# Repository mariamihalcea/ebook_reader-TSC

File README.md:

# OpenBook E-Reader 

## 1. Diagrama bloc

**Descriere:**

- Microcontrollerul **ESP32-C6** este unitatea centrala care gestioneaza comunicarea cu toate modulele periferice.
- Display-ul e-paper este controlat de un circuit dedicat de comanda.
- Senzorul ambiental **BME688** masoara calitatea aerului si temperatura.
- Memoria externa NOR Flash (64MB) si cardul SD permit stocarea fisierelor (eBook-uri, configurari etc).
- RTC-ul **DS3231SN** asigura ora exacta in mod autonom, chiar si in lipsa alimentarii.
- Incarcarea bateriei Li-Po se face prin USB-C, cu protectie ESD si monitorizare a nivelului de incarcare (MAX17048).
- Butoanele fizice permit resetul sistemului si selectii de tip boot.

---

## 2. Bill Of Materials (BOM)
| Componenta | Link | Datasheet |
|-----------|--------------|-----------|
| BUTTON | [Model](https://industry.panasonic.com/global/en/products/control/switch/light-touch/number/evqpuj02k) | [Datasheet](https://www.lcsc.com/datasheet/lcsc_datasheet_2201121800_PANASONIC-EVQPUJ02K_C2936858.pdf) |
| CAPACITOR | [Model](https://componentsearchengine.com/part-view/R0402%201%25%20100%20K%20(RC0402FR-07100KL)/YAGEO) | [Datasheet](//efaidnbmnnnibpcajpcglclefindmkaj/https://www.resistor.com/assets/pdf/0402tstd.pdf) |
| CPH3225A | [Model](https://www.snapeda.com/parts/CPH3225A/Seiko+Instruments/view-part/?ref=eda) | [Datasheet](https://octopart.com/datasheet/cph3225a-seiko-25340571) |
| EVQPUJ02K | [Model](https://industry.panasonic.com/global/en/products/control/switch/light-touch/number/evqpuj02k) | [Datasheet](https://www.lcsc.com/datasheet/lcsc_datasheet_2201121800_PANASONIC-EVQPUJ02K_C2936858.pdf) |
| KP-1608SURCK | [Model](https://www.snapeda.com/parts/KP-1608SURCK/Kingbright/view-part/?ref=search&t=LED%200603) | [Datasheet](//efaidnbmnnnibpcajpcglclefindmkaj/https://media.elv.com/file/107153_led_surck1608_data.pdf) |
| USBLC6-2SC6Y | [Model](https://www.snapeda.com/parts/USBLC6-2SC6Y/STMicroelectronics/view-part/?ref=eda) | [Datasheet](https://www.digikey.com/en/htmldatasheets/production/1375342/0/0/1/usblc6-2sc6y) |
| SD0805S020S1R0 | [Model](https://ro.mouser.com/ProductDetail/KYOCERA-AVX/SD0805S020S1R0?qs=jCA%252BPfw4LHbpkAoSnwrdjw%3D%3D) | [Datasheet](https://www.alldatasheet.com/view.jsp?Searchword=SD0805S&sField=2) |
| PGB1010603MR | [Model](https://www.snapeda.com/parts/PGB1010603MR/Littelfuse/view-part/?ref=eda) | [Datasheet](https://www.alldatasheet.com/view.jsp?Searchword=Pgb1010603mr&gad_source=1&gbraid=0AAAAADcdDU8aYfZtfJfdZ9I5j6RwZ_cbA&gclid=Cj0KCQjwqcO_BhDaARIsACz62vOPBOBe0eOh5gDUFkkKl4JBcbmoFZYtJ8BOnbaWqr_BuUCcVWvbutAaAmGkEALw_wcB) |
| BD5229G-TR  | [Model](https://componentsearchengine.com/part-view/BD5229G-TR/ROHM%20Semiconductor) | [Datasheet](https://www.lcsc.com/datasheet/lcsc_datasheet_2201131330_ROHM-Semicon-BD5229G-TR_C962636.pdf) |
| XC6220A331MR-G | [Model](https://componentsearchengine.com/part-view/XC6220A331MR-G/Torex) | [Datasheet](https://www.alldatasheet.com/view.jsp?Searchword=Xc6220&gad_source=1&gbraid=0AAAAADcdDU8aYfZtfJfdZ9I5j6RwZ_cbA&gclid=Cj0KCQjwqcO_BhDaARIsACz62vPS06NB6tLgniZzfaVpKNu1m811BNk6AEPfg4DbP6f5S8QWA_pW_UQaAv-0EALw_wcB) |
| XC6220A331MR-G | [Model](https://componentsearchengine.com/part-view/XC6220A331MR-G/Torex) | [Datasheet](https://www.alldatasheet.com/view.jsp?Searchword=Xc6220&gad_source=1&gbraid=0AAAAADcdDU8aYfZtfJfdZ9I5j6RwZ_cbA&gclid=Cj0KCQjwqcO_BhDaARIsACz62vMO5_aHsn35cIZBK6oCFuB_WOxz_zKu4yOHJ69-EnaUd5Jfas_Avm8aAuk5EALw_wcB) |
| USB4110-GF-A  | [Model](https://componentsearchengine.com/part-view/USB4110-GF-A/GCT%20(GLOBAL%20CONNECTOR%20TECHNOLOGY)) | [Datasheet](//efaidnbmnnnibpcajpcglclefindmkaj/https://gct.co/files/drawings/usb4110.pdf) |
| Adafruit | [Model](https://eu.mouser.com/ProductDetail/Adafruit/4208?qs=PzGy0jfpSMtbScLbr0L5dw%3D%3D) | [Datasheet](https://www.arrow.com/en/manufacturers/adafruit-industries/datasheets) |
| Bobina | [Model](https://store.comet.srl.ro/Catalogue/Product/43497/) | [Datasheet](https://www.scribd.com/document/814581278/Datasheet-Bobina) |
| PFMF | [Model](https://www.mouser.co.uk/ProductDetail/EPCOS-TDK/B72520T0350K062?qs=dEfas%2FXlABIszF52uu7vrg%3D%3D) | [Datasheet](https://ro.mouser.com/c/ds/circuit-protection/thermistors/resettable-fuses-pptc/?m=Schurter&series=PFMF) |
| DMG2305UX-7 | [Model](https://componentsearchengine.com/part-view/DMG2305UX-7/Diodes%20Incorporated) | [Datasheet](//efaidnbmnnnibpcajpcglclefindmkaj/https://www.mouser.com/datasheet/2/115/DMG2305UX-266242.pdf?srsltid=AfmBOop22k34YTJJra1xubiU6LPiN4M4JlcWbRoSNdxSGFak8uWgXPpK) |
| Si1308EDL-T1-GE3 | [Model](https://componentsearchengine.com/part-view/SI1308EDL-T1-GE3/Vishay) | [Datasheet](https://www.alldatasheet.com/view.jsp?Searchword=Si1308edl&gad_source=1&gbraid=0AAAAADcdDU-px713ONYSnQ2O-gcwqYcFq&gclid=Cj0KCQjwqcO_BhDaARIsACz62vN_Nz3MJOc6J_03gnVBm7aSqC8v9wyP0VD-iRKP-gFrYgdhLi99I14aAlVJEALw_wcB) |
| R0402 | [Model](https://componentsearchengine.com/part-view/R0402%201%25%20100%20K%20(RC0402FR-07100KL)/YAGEO) | [Datasheet](//efaidnbmnnnibpcajpcglclefindmkaj/https://www.resistor.com/assets/pdf/0402tstd.pdf) |
| BME680 | [Model](https://www.snapeda.com/parts/BME680/Bosch/view-part/?welcome=home) | [Datasheet](//efaidnbmnnnibpcajpcglclefindmkaj/https://www.bosch-sensortec.com/media/boschsensortec/downloads/datasheets/bst-bme680-ds001.pdf) |
| SMD Solder | [Model](https://grabcad.com/library/solder-jumpers-1) | [Datasheet]() |
| W25Q512JVEIQ | [Model](https://www.snapeda.com/parts/ESP32-C6-WROOM-1-N8/Espressif+Systems/view-part/?ref=eda) | [Datasheet](//efaidnbmnnnibpcajpcglclefindmkaj/https://www.mouser.com/datasheet/2/949/W25Q512JV_SPI_RevB_06252019_KMS-2487502.pdf?srsltid=AfmBOoquExqDVgxEELF9CzuOGxHos0CD1nQDROHD6Eebdm2foNzqozqU) |
| ESP32-C6-WROOM-1-N8 | [Model](https://www.snapeda.com/parts/ESP32-C6-WROOM-1-N8/Espressif+Systems/view-part/?ref=eda) | [Datasheet](//efaidnbmnnnibpcajpcglclefindmkaj/https://www.mouser.com/catalog/specsheets/Espressif_ESP32_C6_WROOM_1%20_Datasheet_V0.1_PRELIMINARY_en.pdf?srsltid=AfmBOooHQKNitqODRaaPjoZInfWKTacDER1t5uRK6sKqT13TrzvVo_B7) |
| DS3231SN# | [Model](https://www.snapeda.com/parts/DS3231SN%23/Analog+Devices/view-part/?ref=eda) | [Datasheet](https://www.alldatasheet.com/view.jsp?Searchword=Ds3231sn%20datasheet&gad_source=1&gbraid=0AAAAADcdDU-Gy9URfMxGmqiPg7ci5L3wR&gclid=Cj0KCQjwqcO_BhDaARIsACz62vMkK3ETSnW2w7mo0Fa-wgWJGn89AxWCyIND6k5X8MmoPl6hv6VWwT8aAiS-EALw_wcB) |
| MAX17048G+T10 | [Model](https://www.snapeda.com/parts/MAX17048G+T10/Analog+Devices/view-part/?ref=eda) | [Datasheet](https://www.alldatasheet.com/view.jsp?Searchword=Max17048&gad_source=1&gbraid=0AAAAADcdDU8aYfZtfJfdZ9I5j6RwZ_cbA&gclid=Cj0KCQjwqcO_BhDaARIsACz62vNa9xrVfzjCjADRwXD0RBbo4Nret3ywwteDGLJKZui8ZL8KdVlTE7caAvQxEALw_wcB) |
| MCP73831T-5ACI/OT | [Model](https://www.mouser.co.uk/ProductDetail/Microchip-Technology/MCP73831T-5ACI-OT?qs=hH%252BOa0VZEiAcgAcEkuamXg%3D%3D) | [Datasheet](//efaidnbmnnnibpcajpcglclefindmkaj/https://ww1.microchip.com/downloads/en/DeviceDoc/MCP73831-Family-Data-Sheet-DS20001984H.pdf) |

## 3. Descriere hardware detaliata

###  Microcontroller – ESP32-C6
- Controleaza toate componentele externe prin GPIO, I2C, SPI.

### E-paper Display + Driver
- Controlat prin SPI, cu tensiune separata de alimentare si control.

###  RTC – DS3231SN
- Ceas in timp real cu precizie mare si backup pe baterie.
- Comunicatie I2C cu ESP32-C6.
- Folosit pentru afisarea orei si sincronizare evenimente programate.

### Card SD
- Legat la ESP32 prin SPI.
- Utilizat pentru incarcare/citire fisiere eBook, configurari etc.

###  Senzor mediu – BME688
- Comunica prin I2C.
- Masoara temperatura, presiune, umiditate si compusi volatili.

###  Conector USB-C
- Folosit pentru incarcare si posibila conectare seriala cu PC pentru debug.

##  4. Conexiuni ESP32-C6

| Componenta            | Pin ESP32-C6      | Interfata | Motiv utilizare                      |
|----------------------|-------------------|-----------|--------------------------------------|
| E-paper Display       | IO06, IO07, IO08  | SPI       | Transfer rapid de date catre display |
| Flash NOR             | IO10, IO11, IO12  | SPI       | Stocare externa rapida               |
| Senzor BME688         | IO18 (SDA), IO19 (SCL) | I2C   | Comunicare cu senzori               |
| RTC DS3231SN          | IO18, IO19        | I2C       | Reutilizeaza magistrala I2C         |
| MAX17048 (Baterie)    | IO18, IO19        | I2C       | Monitor baterie, I2C comun           |
| SD Card               | IO01, IO02, IO03  | SPI       | Citire fisiere eBook                 |
| Buton reset/boot      | IO00, EN          | GPIO      | Control boot si reset manual        |

---

## 5. Pasi de implementare

### 1. Analiza documentatiei initiale
Am analizat schematicul si layout-ul placii furnizate de profesor. Pe baza acestora, am recreat designul electronic in Fusion Electronics, atat schema electrica, cat si placa PCB.

### 2. Plasarea componentelor pe PCB
Am asezat componentele pe placa, urmarind o pozitionare si orientare optime, pentru a permite o rutare eficienta si functionala.

### 3. Rutarea traseelor
Traseele de alimentare au fost rutate manual pentru a asigura robustete si dimensiuni corecte. Conexiunile ramase au fost rutate automat, folosind functia de autorouting pe ambele straturi (top si bottom). Am adaugat polygon pour pentru a crea plane de masa pe ambele straturi.

### 4. Optimizarea layout-ului
Am folosit vias pentru a conecta planele de masa intre straturi si pentru a completa zonele neconectate. Am aplicat via stitching pentru a imbunatati integritatea electrica a designului.

### 5. Generarea modelului 3D al placii
Pe baza designului 2D, am generat modelul 3D al placii. Am cautat si importat manual fiecare componenta 3D, pozitionandu-le conform plasamentului din PCB-ul 2D. Pentru componenta *test pad*, neavand un model disponibil online, am creat manual unul pentru a reprezenta corect placa in ansamblu.

### 6. Integrarea in ansamblul final – OpenBook Enclosure
Am importat modelul 3D al placii in fisierul principal al carcasei (OpenBook Enclosure). Acolo am plasat toate componentele in carcasa finala pentru a asigura o potrivire corecta si functionala. Display-ul si bateria au fost desenate manual pentru a fi integrate in ansamblu si pentru a oferi o reprezentare cat mai realista a produsului final.
##  6. Alte detalii relevante

La realizarea PCB-ului am intampinat si doua erori de Copper Width, desi aveam  dimensiunile corespunzatoare, asa ca le-am aprobat.

<br>
si doua erori din cauza dimensiunii gaurilor din mufa USB, pe care de asemenea le am aprobat

---

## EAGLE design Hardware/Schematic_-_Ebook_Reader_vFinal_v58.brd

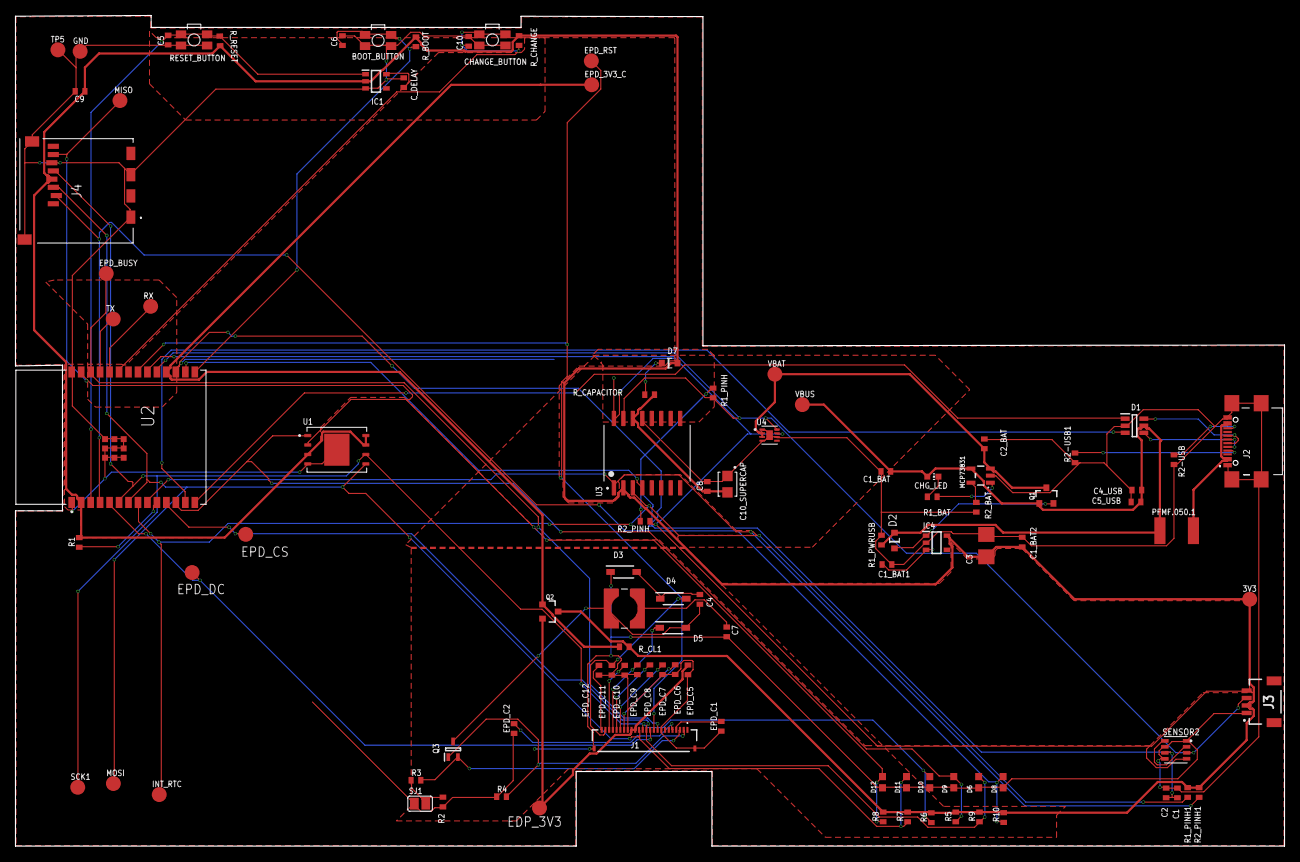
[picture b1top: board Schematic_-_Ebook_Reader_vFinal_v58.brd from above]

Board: 2 copper layers, 170.2 x 111.4 mm, 103 parts (0 on the bottom side), 57 nets.

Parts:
3V3: TPTP20R; TP20R
BOOT_BUTTON: BUTTON_CUSYOMV1; MYBUTTON
C1, C2, C4_USB, C6, C8, C9, C10: 100nF; EAGLE-LTSPICE_C0402
C1_BAT, C1_BAT1, C1_BAT2, C2_BAT, C5_USB: 4.7uF; EAGLE-LTSPICE_C0402
C3: 100uF TANT; RCL_CT3528
C4: 4.7uF/25V; EAGLE-LTSPICE_C0402
C5: 1uF; EAGLE-LTSPICE_C0402
C7: 10uF; EAGLE-LTSPICE_C0402
C10_SUPERCAP: CPH3225A; CAPCP3225X100N
CHANGE_BUTTON: BUTTON_CUSYOMV1; MYBUTTON
CHG_LED: ADAFRUIT_CHIP-LED0603
C_DELAY: 100nF; EAGLE-LTSPICE_C0402
D1: USBLC6-2SC6Y; SOT95P280X145-6N
D2, D7: ESP32_WROVER_AVX---SD0805S020S1R0_AVX_SD0805S020S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; ESP32_WROVER_AVX---SD0805S020S1R0_AVX_SD0805S020S1R0_0
D3, D4, D5: MBR0530; SOD3716X135N
D6, D8, D9, D10, D11, D12: PGB1010603MR; DIOC1608X36N
EDP_3V3: TPTP20R; TP20R
EPD_3V3_C: TPTP20R; TP20R
EPD_BUSY: TPTP20R; TP20R
EPD_C1, EPD_C2, EPD_C6, EPD_C7, EPD_C8, EPD_C9, EPD_C10, EPD_C11: 1uF_50V; EAGLE-LTSPICE_C0402
EPD_C5: 0.1uF_50V; EAGLE-LTSPICE_C0402
EPD_C12: 1uF/50v; EAGLE-LTSPICE_C0402
EPD_CS: TPTP20R; TP20R
EPD_DC: TPTP20R; TP20R
EPD_RST: TPTP20R; TP20R
GND: TPTP20R; TP20R
IC1: BD5229G-TR; SOT95P280X125-5N
IC4: XC6220A331MR-G; SOT95P280X120-5N
INT_RTC: TPTP20R; TP20R
J1: FH34SRJ-24S-0.5SH_99_; FH34SRJ24S05SH99
J2: SAMACSYS_PARTS_USB4110-GF-A; SAMACSYS_PARTS_USB4110GFA
J3: QWIIC_RIGHT_ANGLE; JST04_1MM_RA
J4: 112A-TAAR-R03_ATTEND; 112ATAARR03ATTEND
L1: 68uH; IND_4828-WE-TPC_WRE
MCP73831: ESP32_WROVER_SPARKFUN-IC-POWER_MCP73831; ESP32_WROVER_SPARKFUN-IC-POWER_SOT23-5
MISO: TPTP20R; TP20R
MOSI: TPTP20R; TP20R
PFMF.050.1: ESP32C6_VARISTORCN1812; ESP32C6_VARISTOR_CT/CN1812
Q1, Q2: 20V/4.2A/52mΩ/1.4W; ESP32_WROVER_SPARKFUN-DISCRETESEMI_SOT23-3
Q3: SI1308EDL-T1-GE3; SOT65P210X110-3N
R1, R1_PINH, R1_PINH1, R4, R5, R6, R7, R8, R9, R10: 10K; ESP32_WROVER_EAGLE-LTSPICE_R0402
R1_BAT: 200; ESP32_WROVER_EAGLE-LTSPICE_R0402
R1_PWRUSB: 100K; ESP32_WROVER_EAGLE-LTSPICE_R0402
R2: 2.2; ESP32_WROVER_EAGLE-LTSPICE_R0402
R2-USB, R2-USB1: 5k1; ESP32_WROVER_EAGLE-LTSPICE_R0402
R2_BAT: 2K; ESP32_WROVER_EAGLE-LTSPICE_R0402
R2_PINH, R2_PINH1: 10k; ESP32_WROVER_EAGLE-LTSPICE_R0402
R3: 0.47; ESP32_WROVER_EAGLE-LTSPICE_R0402
RESET_BUTTON: BUTTON_CUSYOMV1; MYBUTTON
RX: TPTP20R; TP20R
R_BOOT: 10K; ESP32_WROVER_EAGLE-LTSPICE_R0402
R_CAPACITOR: 15; ESP32_WROVER_EAGLE-LTSPICE_R0402
R_CHANGE: 10K; ESP32_WROVER_EAGLE-LTSPICE_R0402
R_CL1: 10k; ESP32_WROVER_EAGLE-LTSPICE_R0402
R_RESET: 10K; ESP32_WROVER_EAGLE-LTSPICE_R0402
SCK1: TPTP20R; TP20R
SENSOR2: BME688; ESP32_WROVER_BME680_PSON80P300X300X100-8N
SJ1: SJ
TP5: TPTP20R; TP20R
TX: TPTP20R; TP20R
U1: W25Q512JVEIQ; SON127P600X800X80-9N
U2: ESP32-C6-WROOM-1-N8; XCVR_ESP32-C6-WROOM-1-N8
U3: DS3231SN#; SOIC127P1032X265-16N
U4: MAX17048G+T10; SON50P200X200X80-9N
VBAT: TPTP20R; TP20R
VBUS: TPTP20R; TP20R

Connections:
3V3: 3V3.TP, C1_BAT2.1, C3.+, C9.1, D7.2, IC1.2, IC4.5, J3.2, J4.P4, Q2.3, R1.2, R1_PINH1.2, R2_PINH1.2, R5.2, R6.2, R7.2, R8.2, R9.2, R10.2, R_BOOT.2, R_CHANGE.2, R_CL1.2, R_RESET.2, U1.3, U1.7, U1.8, U2.2, U3.2
32KHZ: R2_PINH1.1, U2.9, U3.1
DN: D1.4, J2.A7, J2.B7
DP: D1.6, J2.A6, J2.B6
EPD_3V3: EDP_3V3.TP, EPD_C5.2, J1.15, J1.16, Q2.2
EPD_3V3_C: EPD_3V3_C.TP, Q2.1, R_CL1.1, U2.18
EPD_BUSY: EPD_BUSY.TP, J1.9, U2.26
EPD_CS: D6.2, EPD_CS.TP, J1.12, R9.1, U2.11
EPD_DC: EPD_DC.TP, J1.11, U2.5
EPD_RST: EPD_RST.TP, J1.10, U2.21
FLASH_CS: D9.2, R5.1, U1.1, U2.12
GDR: J1.2, Q3.1, R4.2
GND: BOOT_BUTTON.1, BOOT_BUTTON.2, C1.2, C1_BAT.2, C1_BAT1.2, C1_BAT2.2, C2.2, C2_BAT.2, C3.-, C4_USB.2, C5.2, C5_USB.2, C6.2, C7.2, C8.2, C9.2, C10.2, C10_SUPERCAP.1, CHANGE_BUTTON.1, CHANGE_BUTTON.2, C_DELAY.2, D1.2, D3.1, D6.1, D8.1, D9.1, D10.1, D11.1, D12.1, EPD_C1.1, EPD_C2.1, EPD_C5.1, EPD_C6.1, EPD_C7.1, EPD_C9.1, EPD_C10.1, EPD_C11.1, EPD_C12.1, GND.TP, IC1.3, IC4.2, J1.8, J1.17, J1.MP1, J1.MP2, J2.A1, J2.A12, J2.B1, J2.B12, J2.MP1, J2.MP2, J2.MP3, J2.MP4, J3.1, J4.G1, J4.G2, J4.G3, J4.G4, J4.P6, MCP73831.2, R1_PWRUSB.2, R2.1, R2-USB.2, R2-USB1.1, R2_BAT.1, R4.1, RESET_BUTTON.1, RESET_BUTTON.2, SENSOR2.1, SENSOR2.5, SENSOR2.7, SJ1.1, TP5.TP, U1.4, U1.9, U2.1, U2.28, U2.29_1, U2.29_2, U2.29_3, U2.29_4, U2.29_5, U2.29_6, U2.29_7, U2.29_8, U2.29_9, U3.13, U4.1, U4.4, U4.6, U4.9
GPIO8: R1.1, U2.10
I2C_PW: C1.1, C2.1, R1_PINH.2, R2_PINH.2, SENSOR2.6, U2.17
INT_RTC: INT_RTC.TP, R1_PINH1.1, U2.8, U3.3
IO/BOOT: BOOT_BUTTON.3, BOOT_BUTTON.4, C6.1, R_BOOT.1, U2.15
IO/CHANGE: C10.1, CHANGE_BUTTON.3, CHANGE_BUTTON.4, R_CHANGE.1, U2.23
MISO: D12.2, J4.P7, MISO.TP, R8.1, U1.2, U2.27
MOSI: D11.2, J1.14, J4.P3, MOSI.TP, R7.1, U1.5, U2.7
unnamed: C1_BAT1.1, D2.1, IC4.1, IC4.3, Q1.2
unnamed: EPD_C2.2, J1.5
unnamed: J2.A5, R2-USB1.2
unnamed: C7.1, L1.2
unnamed: MCP73831.1, R1_BAT.2
unnamed: CHG_LED.C, R1_BAT.1
unnamed: C4.1, D3.2, D4.1
unnamed: MCP73831.5, R2_BAT.2
unnamed: C_DELAY.1, IC1.5
unnamed: D7.1, R_CAPACITOR.1
unnamed: EPD_C1.2, J1.4
unnamed: SENSOR2.2, SENSOR2.8
unnamed: J2.B5, R2-USB.1
unnamed: EPD_C6.2, J1.18
unnamed: EPD_C7.2, J1.19
unnamed: EPD_C8.2, J1.20
unnamed: EPD_C10.2, J1.22
unnamed: EPD_C12.2, J1.24
PREVGH: D5.1, EPD_C9.2, J1.21
PREVGL: D4.2, EPD_C11.2, J1.23
RESE: J1.3, Q3.2, R3.2
RESE': R2.2, R3.1, SJ1.2
RESET: C5.1, IC1.1, RESET_BUTTON.3, RESET_BUTTON.4, R_RESET.1, U2.3
RTC_RST: U2.16, U3.4
RX: RX.TP, U2.24
SCK: D10.2, J1.13, J4.P5, R6.1, SCK1.TP, U1.6, U2.6
SCL: J3.4, R2_PINH.1, SENSOR2.4, U2.20, U3.16, U4.7
SDA: J3.3, R1_PINH.1, SENSOR2.3, U2.19, U3.15, U4.8
SRC: C4.2, D5.2, L1.1, Q3.3
SS_SD: D8.2, J4.P2, R10.1, U2.4
TX: TX.TP, U2.25
USB_D+: D1.1, U2.14
USB_D-: D1.3, U2.13
VBAT: C2_BAT.1, MCP73831.3, Q1.3, U4.2, U4.3, VBAT.TP
VBUS: C1_BAT.1, C4_USB.1, C5_USB.1, CHG_LED.A, D1.5, D2.2, MCP73831.4, PFMF.050.1.2, Q1.1, R1_PWRUSB.1, VBUS.TP
VRTC: C8.1, C10_SUPERCAP.2, R_CAPACITOR.2, U3.14
VUSB: J2.A4, J2.A9, J2.B4, J2.B9, PFMF.050.1.1

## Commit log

2025-04-06 Create z
2025-04-06 Create file
2025-04-06 Create img
2025-04-06 Create License
2025-04-14 Hardware updated
2025-04-14 Images updated
2025-04-14 Mechanical updated

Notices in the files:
parts and their libraries:
COPYRIGHT: Copyright (C) 2024 Ultra Librarian. All rights reserved.
